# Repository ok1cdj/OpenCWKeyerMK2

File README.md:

# OpenCWKeyerMK2

Hardware for K3NG Arduino keyer https://github.com/k3ng/k3ng_cw_keyer

KIT is available from https://www.hamshop.cz/open-cw-keyer-c27/open-cw-keyer-i196/

Documentation https://github.com/ok1cdj/OpenCWKeyerMK2/wiki

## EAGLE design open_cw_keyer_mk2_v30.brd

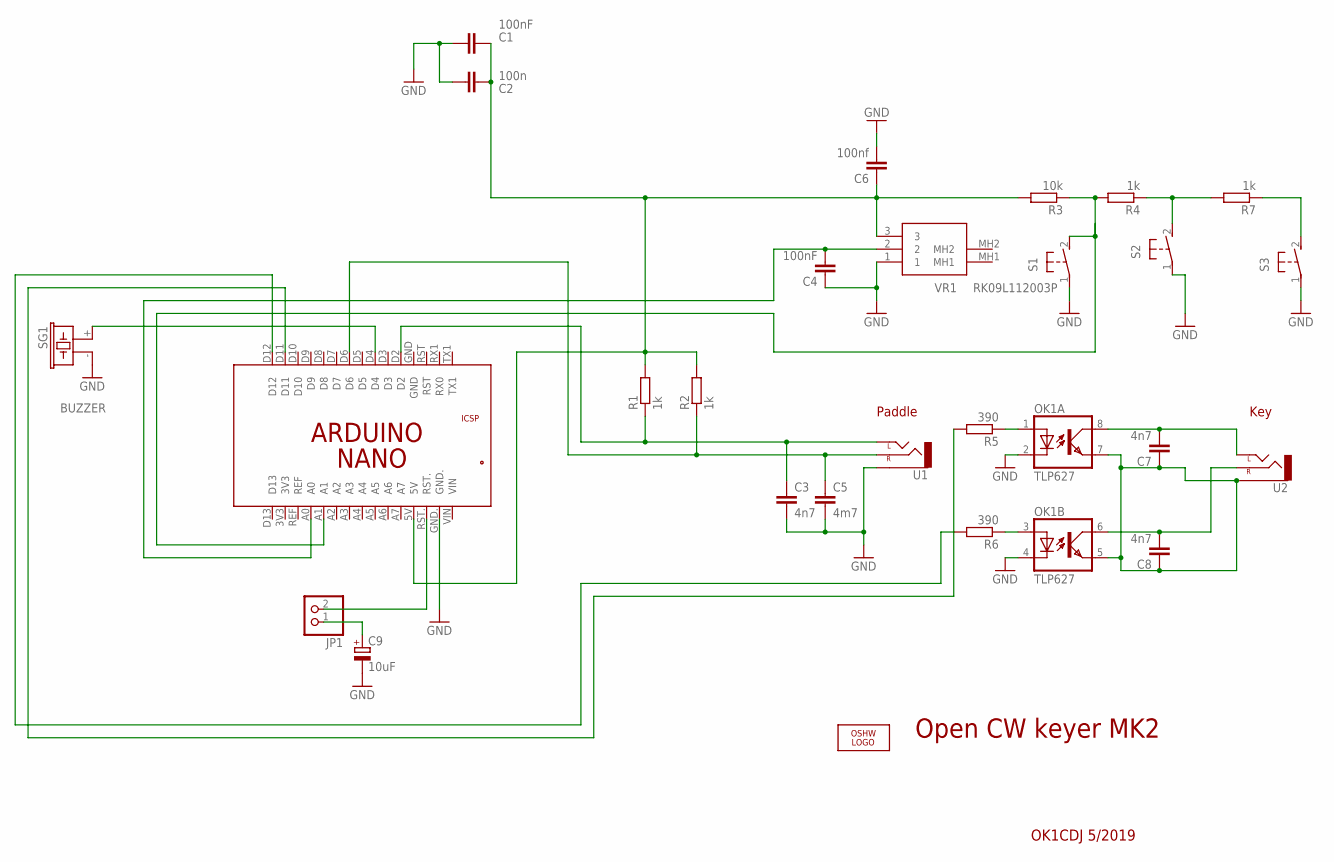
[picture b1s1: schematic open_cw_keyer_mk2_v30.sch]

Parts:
C1, C4: 100nF; C0805
C2: 100n; C0805
C3: 4n7; C0805
C5: 4m7; C0805
C6: 100nf; C0805
C7, C8: 4n7; C0805K
C9: 10uF; B/3528-21R
JP1: PINHD-1X2/90; 1X02/90
LOGO1: OSHW_LOGO_FILLX0150-NT; OSHW_FILLX150_NOTEXT
OK1: TLP627; DIL08
PCB1: ARDUINO_NANO
R1, R2, R4, R7: 1k; M0805
R3: 10k; M0805
R5, R6: 390; M0805
S1, S2, S3: 31-XX; B3F-31XX
SG1: BUZZER; F/CM12P
U1, U2: AUDIO-JACKPTH; AUDIO-JACK
VR1: RK09L112003P

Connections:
5V: C1.1, C2.1, C6.1, PCB1.5V, R1.2, R2.2, R3.2, VR1.3
GND: C1.2, C2.2, C3.2, C4.1, C5.2, C6.2, C9.-, OK1.2 (C), OK1.4 (C), PCB1.GND., S1.1, S2.1, S3.1, SG1.- (2), U1.SLEEVE, VR1.1
unnamed: C3.1, PCB1.D2, R1.1, U1.TIP (LEFT)
unnamed: PCB1.D4, SG1.+ (1)
unnamed: JP1.2, PCB1.RST.
unnamed: R4.1, R7.2, S2.2 (S)
unnamed: OK1.1 (A), R5.1
unnamed: OK1.3 (A), R6.1
unnamed: C9.+, JP1.1
unnamed: C7.2, OK1.8 (COL), U2.TIP (LEFT)
unnamed: C8.2, OK1.6 (COL), U2.RING (RIGHT)
unnamed: R7.1, S3.2 (S)
unnamed: C7.1, C8.1, OK1.5 (EMIT), OK1.7 (EMIT), U2.SLEEVE
unnamed: C5.1, PCB1.D6, R2.1, U1.RING (RIGHT)
unnamed: PCB1.D11, R5.2
unnamed: PCB1.D12, R6.2
POT: C4.2, PCB1.A0, VR1.2
TL: PCB1.A1, R3.1, R4.2, S1.2 (S)

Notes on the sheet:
Open CW keyer MK2
Paddle
Key
OK1CDJ 5/2019

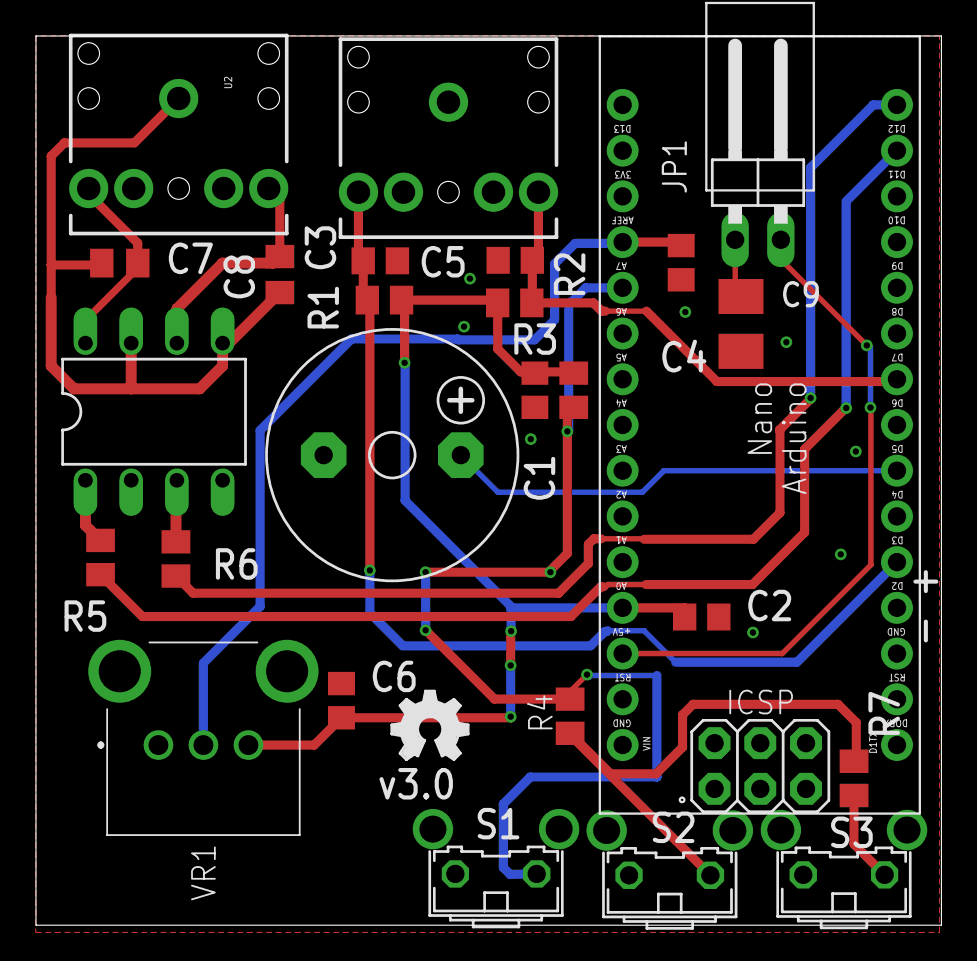
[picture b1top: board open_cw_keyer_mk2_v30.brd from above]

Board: 2 copper layers, 50.3 x 49.4 mm, 27 parts (0 on the bottom side), 18 nets.

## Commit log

2019-05-13 Schematic and PCB pictures
2019-05-15 Pictures
2019-05-15 Eagle files for main board
2019-05-16 Front and rear panels
2019-05-27 Create images
2019-05-27 Create index
2019-05-27 Images for building instructions
